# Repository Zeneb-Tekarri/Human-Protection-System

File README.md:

# Human-Protection-System
PFA 2020

# Project Description: 

**Institution:  
Ministry of Higher Education, Scientific Research, and Technology  
University of Sousse  
Higher Institute of Applied Sciences and Technology of Sousse (ISSATS)

**Project Title: 
Mini-Project: "Human Protection Against Gas and Flame"

**Conducted by: 
- Djelassi Chaima  
- Tekarri Zeneb  

**Supervised by: 
Mr. Chebbi Thameur  

**Academic Year: 
2020/2021

## Project Overview ##

The "Human Protection Against Gas and Flame" project is a comprehensive initiative aimed at enhancing human safety by designing an embedded system for the detection of hazardous gases and flames. This system is crucial due to the alarming rates of fatalities caused by gas asphyxiation and burns in Tunisia, especially during the winter season. The primary goal is to mitigate these risks by leveraging modern microelectronics and microcomputing technologies, particularly through the use of Arduino boards and various sensors.

## Objectives ##

1. Detection of Hazardous Gases:
   - Utilize MQ2 gas sensors to detect gases like carbon monoxide (CO), methane (CH4), propane, butane, and other harmful substances.
   - Implement sensitivity adjustments to ensure accurate and timely detection.

2. Flame Detection: 
   - Employ flame sensors that are sensitive to specific wavelengths and frequencies of light emitted by flames to accurately identify the presence of open fire.

3. Alert Mechanisms:
   - Integrate visual (LEDs) and auditory (buzzers) alert systems to notify users of detected hazards.
   - Use GSM modules for remote alerts via SMS or calls.

4. Preventive Measures: 
   - Install fans to reduce gas concentration in the event of a leak.
   - Use servomotors for mechanical actions such as shutting off gas supply.

## System Components ##

- Arduino Uno: The core microcontroller board used for processing inputs from sensors and controlling output devices.
  
- MQ2 Gas Sensors: Semi-conductor sensors that detect various gases and smoke, providing rapid measurements and adjustable sensitivity.

- Flame Sensors: Devices designed to detect light from flames, distinguishing it from other light sources by focusing on specific optical wavelengths.

- LED Indicators: Green, yellow, and red LEDs provide visual alerts based on the type and severity of the detected hazard.

- Buzzers: Emit sound alarms to alert users of danger.

- Fans and Servomotors: 
   Fans help ventilate areas to disperse harmful gases.
   Servomotors perform mechanical operations to prevent further hazards.

- GSM Module (SIM900): Allows the system to send notifications and alerts via SMS, enhancing remote monitoring capabilities.

## Software and Simulation ##

- Arduino Software (IDE): An open-source platform used for programming the Arduino board and managing its inputs and outputs.
  
- Proteus 8 Professional (ISIS): A software tool for simulating and testing the embedded system’s circuit designs.

- KiCad: Used for designing and visualizing the electronic circuits of the project.

## Conclusion ##

This project represents a vital step towards improving safety measures against gas leaks and fire hazards in domestic, industrial, and educational settings. By integrating modern technology with practical safety solutions, the project aims to provide a reliable system that can preemptively alert users, thus preventing potential accidents and saving lives.

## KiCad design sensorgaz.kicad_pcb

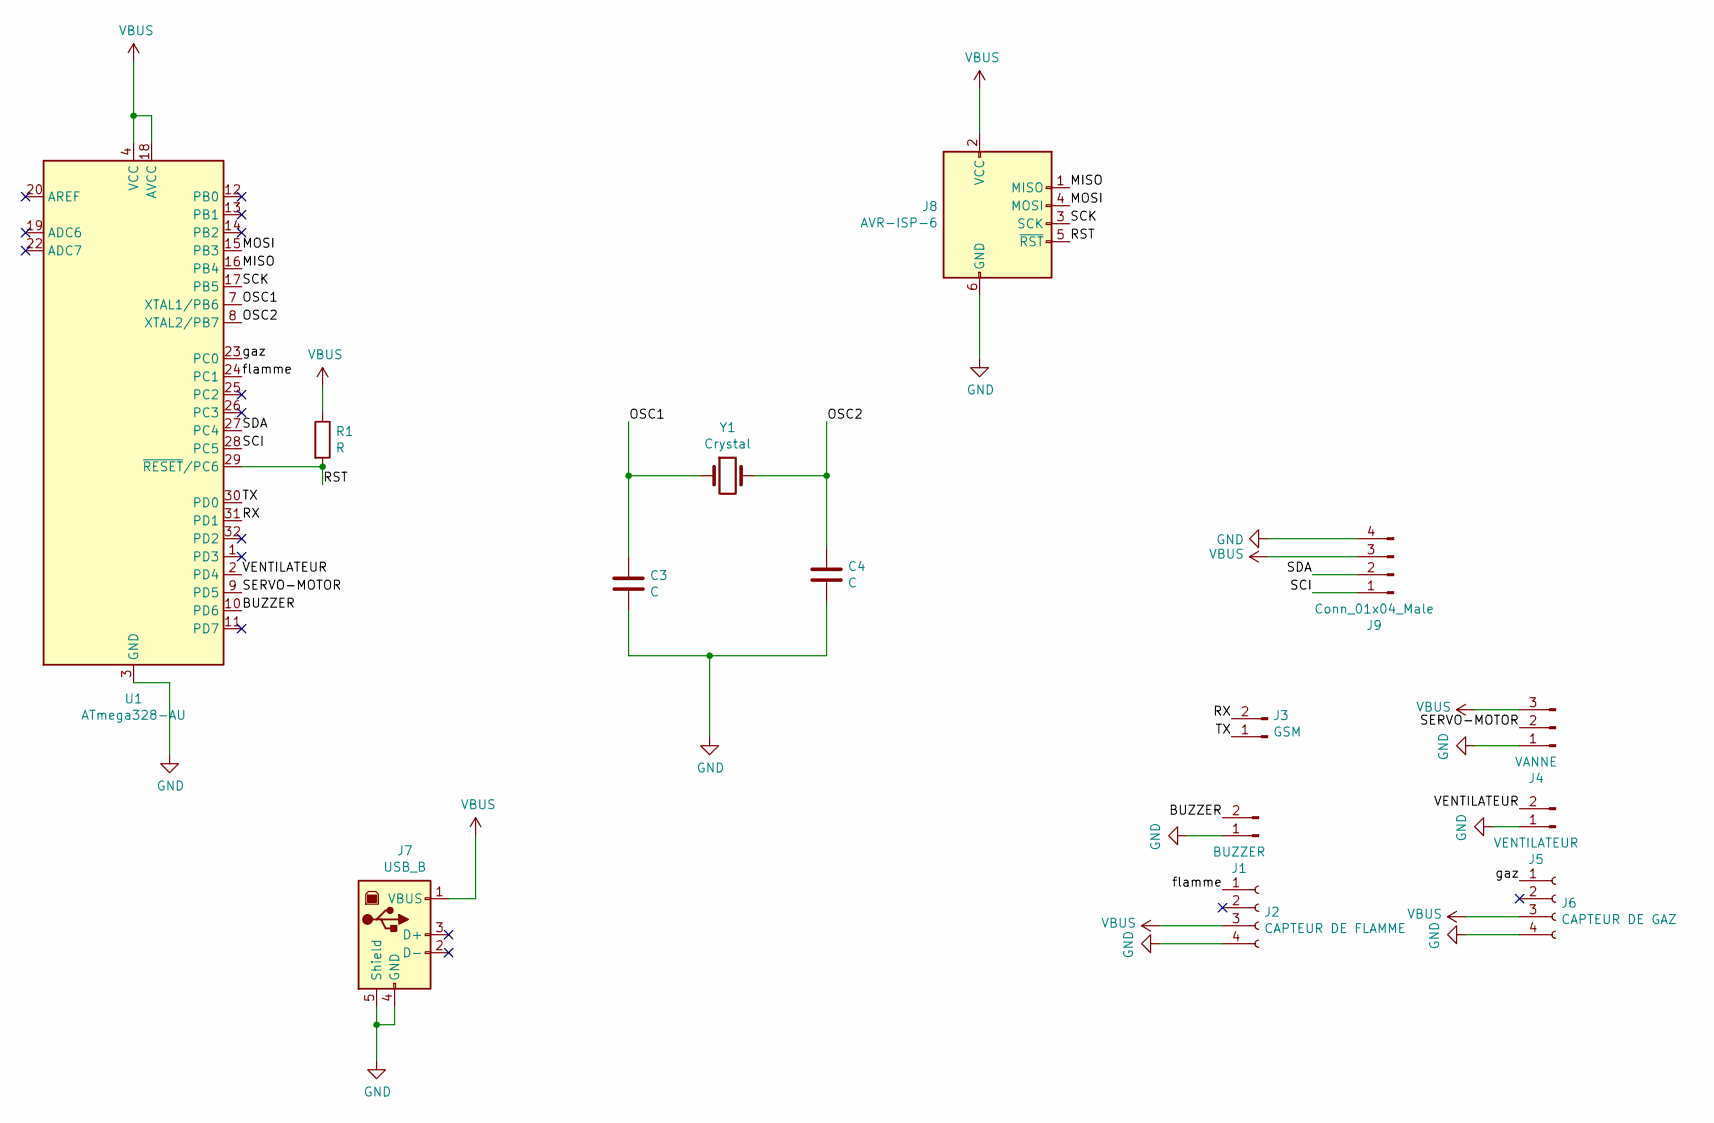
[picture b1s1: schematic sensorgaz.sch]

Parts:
C3, C4: C; C_Disc_D3.0mm_W2.0mm_P2.50mm
J1: BUZZER; JST_EH_B2B-EH-A_1x02_P2.50mm_Vertical
J2: CAPTEUR DE FLAMME; JST_EH_B4B-EH-A_1x04_P2.50mm_Vertical
J3: GSM; JST_EH_B2B-EH-A_1x02_P2.50mm_Vertical
J4: VANNE; JST_EH_B3B-EH-A_1x03_P2.50mm_Vertical
J5: VENTILATEUR; JST_EH_B2B-EH-A_1x02_P2.50mm_Vertical
J6: CAPTEUR DE GAZ; JST_EH_B4B-EH-A_1x04_P2.50mm_Vertical
J7: USB_B; USB_B_OST_USB-B1HSxx_Horizontal
J8: AVR-ISP-6; IDC-Header_2x03_P2.54mm_Vertical
J9: Conn_01x04_Male; TE_MATE-N-LOK_350211-1_1x04_P5.08mm_Vertical
R1: R; R_Axial_DIN0204_L3.6mm_D1.6mm_P1.90mm_Vertical
U1: ATmega328-AU; TQFP-32_7x7mm_P0.8mm
Y1: Crystal; Crystal_HC49-U_Vertical

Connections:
/BUZZER: J1.2, U1.10 (PD6)
/MISO: J8.1 (MISO), U1.16 (PB4)
/MOSI: J8.4 (MOSI), U1.15 (PB3)
/OSC1: C3.1, U1.7 (XTAL1/PB6), Y1.1
/OSC2: C4.1, U1.8 (XTAL2/PB7), Y1.2
/RST: J8.5 (~RST), R1.2, U1.29 (~RESET~/PC6)
/RX: J3.2, U1.31 (PD1)
/SCI: J9.1, U1.28 (PC5)
/SCK: J8.3 (SCK), U1.17 (PB5)
/SDA: J9.2, U1.27 (PC4)
/SERVO-MOTOR: J4.2, U1.9 (PD5)
/TX: J3.1, U1.30 (PD0)
/VENTILATEUR: J5.2, U1.2 (PD4)
/flamme: J2.1, U1.24 (PC1)
/gaz: J6.1, U1.23 (PC0)
GND: C3.2, C4.2, J1.1, J2.4, J4.1, J5.1, J6.4, J7.4 (GND), J7.5 (Shield), J8.6 (GND), J9.4, U1.3 (GND), U1.5 (GND), U1.21 (GND)
VBUS: J2.3, J4.3, J6.3, J7.1 (VBUS), J8.2 (VCC), J9.3, R1.1, U1.4 (VCC), U1.6 (VCC), U1.18 (AVCC)

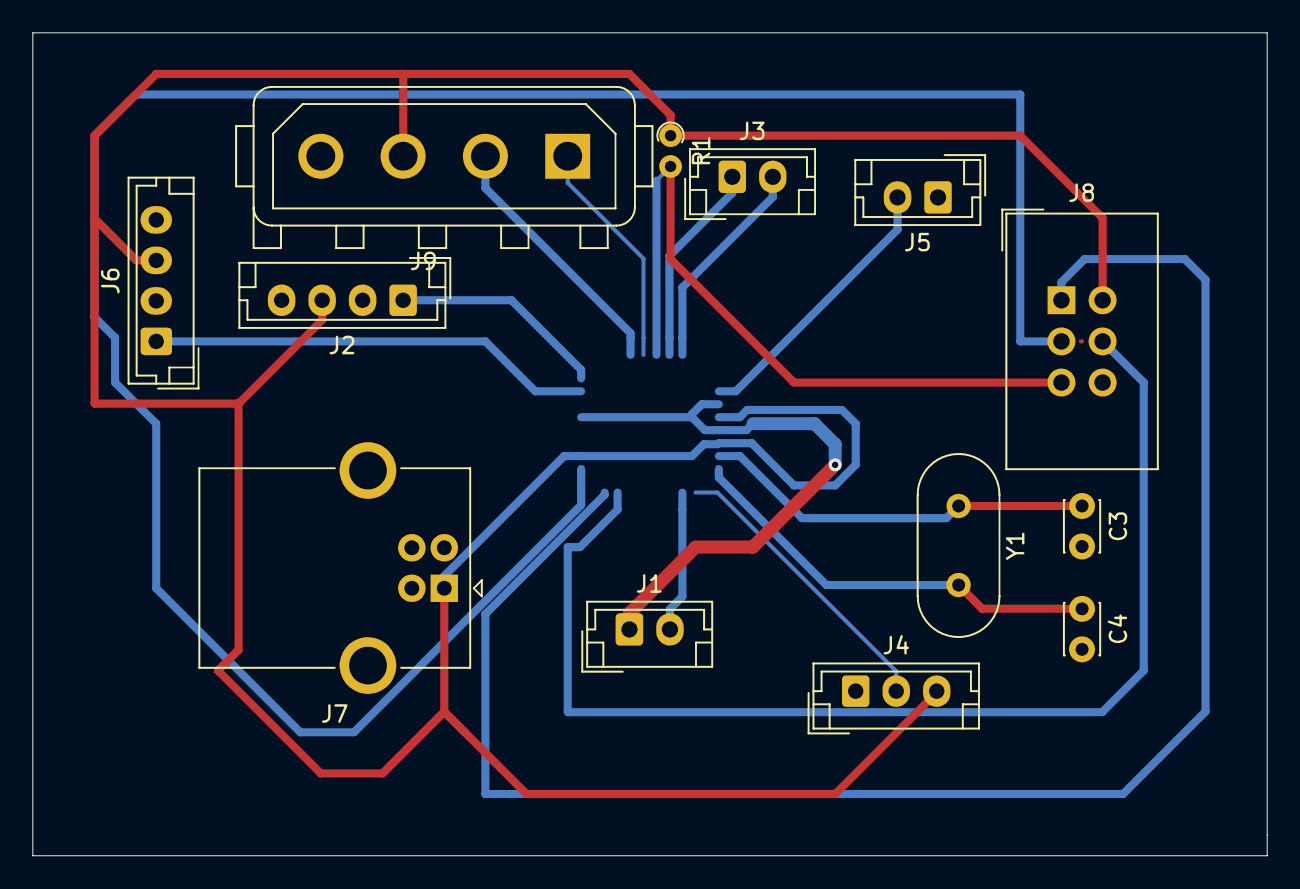
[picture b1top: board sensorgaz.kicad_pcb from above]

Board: 2 copper layers, 76.2 x 50.8 mm, 14 parts (1 on the bottom side), 17 nets.

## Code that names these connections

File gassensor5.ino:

  #include <SoftwareSerial.h> //bibliotheque du module GSM
#include <Servo.h> //cette bibliotheque  servo est nécessaire pour contrôler le servomoteur.     
Servo monServomoteur; // Créer un objet servo pour nous permettre de contrôler le servomoteur. 
SoftwareSerial gsm (9,10); // rx ,tx 
const unsigned long eventInterval = 6000; 
unsigned long previousTime = 0;//Type de données: unsigned long . c'est le nombre de millisecondes écoulées depuis le démarrage du programme. 
int  flag = 0 ;
void setup() { 
monServomoteur.attach(7);
pinMode(4,OUTPUT); // buzzer
pinMode(8,OUTPUT);// LED rouge
pinMode(11,OUTPUT);//LED vert
pinMode(12,OUTPUT);//LED jaune
pinMode(5,OUTPUT);//ventilateur
pinMode(A0,INPUT); // capteur de gaz
pinMode(A1,INPUT);// capteur de flame 
Serial.begin (9600); // définit la vitesse des transferts que notre programme va effectuer.
gsm.begin(9600); 
}
void loop() { 
if (analogRead(A0)<400 && analogRead(A1)<400){
 flag =0 ;
 Serial.print("no risk\r"); //affichage des messages
 digitalWrite(11,HIGH); // la led verte est allumée
 digitalWrite(8,LOW);  // la led rouge est éteinte
 digitalWrite(12,LOW);// led jaune est éteinte 
 digitalWrite(4,LOW);// buzzer désactivé
 digitalWrite(5,LOW);//ventilateur désactivé
 for (int position = 90; position >= -90; position--) {
    monServomoteur.write(position); }// Fait bouger le bras de 180° à 0°
delay(1000);}
while (analogRead(A0)>300  && analogRead(A1)<400 && flag == 0){
 flag = 1 ;
 digitalWrite(11,LOW);//la led verte est éteinte
  digitalWrite(8,LOW);//la led rouge est éteinte
 digitalWrite(12,HIGH);// la led jaune est allumée
 digitalWrite(8,LOW);//la led rouge est éteinte
 digitalWrite(4,HIGH); // buzzer actif
 digitalWrite(5,HIGH);//ventilateur actif
 for (int position = -180; position <= 180; position++) {
  monServomoteur.write(position);  }// Fait bouger le bras de 0° à 180°
  delay(100);
  Serial.println("AT");// affichage de commande AT
  gsm.println ("AT");
  delay(100);
  gsm.print("AT+CMGF = 1\r");                        //    Mode Texte
  delay (100);
  gsm.println("AT+CMGS = \"+21623171934\"");       // Numéro du consommateur
  delay (100);
  gsm.print("fuite de gaz detecte");// SMS Texte 
  delay(100);
  Serial.print((char) 26); 
  gsm.write((char) 26);                 // CTRL-Z
  delay (100);
  gsm.println();  
  Serial.println();  
  break ; }
  unsigned long currentTime = millis(); //La fonction millis renvoie le nombre de millisecondes pendant lesquelles notre carte Arduino a été mise sous tension.
  if ( currentTime - previousTime >= eventInterval&& analogRead(A0)>400 && analogRead(A1)<400 ) {
   previousTime = currentTime;   // Mettre à jour le timing pour la prochaine fois
   flag = 0 ;}
  else if ( currentTime - previousTime >= eventInterval && analogRead(A0)>400 && analogRead(A1)>400 )
   {previousTime = currentTime;// Mettre à jour le timing pour la prochaine fois
   flag =0; }
 while (analogRead(A1)>400 && analogRead(A0)>400 && flag == 0 ){
  flag = 1;
 digitalWrite(8,HIGH);//la led rouge est allumée 
 digitalWrite(12,HIGH);//la led jaune est allumée
 digitalWrite(11,LOW);//la led verte est éteinte
 digitalWrite(4,HIGH);// buzzer actif
 digitalWrite(5,LOW);//ventilatteur actif
  for (int position = -180; position <= 180; position++) { 
  monServomoteur.write(position);}   // Fait bouger le bras de 0° à 180° 
  Serial.println("AT");
  gsm.println ("AT");
  delay(100); 
  gsm.println("AT+CMGF = 1");                         //  Mode Texte 
  delay (100);
  gsm.println("AT+CMGS = \"+21650863290\"");     // le numero du protection civile 
  delay (100);
  gsm.println (" il y a un feu danger dans la rue de kalaa soghra"); // text SMS
  Serial.print((char) 26);
  gsm.print((char) 26);                 // CTRL-Z
  delay (100);
  gsm.println();
  Serial.println();
  delay(100);
  break ;}}
